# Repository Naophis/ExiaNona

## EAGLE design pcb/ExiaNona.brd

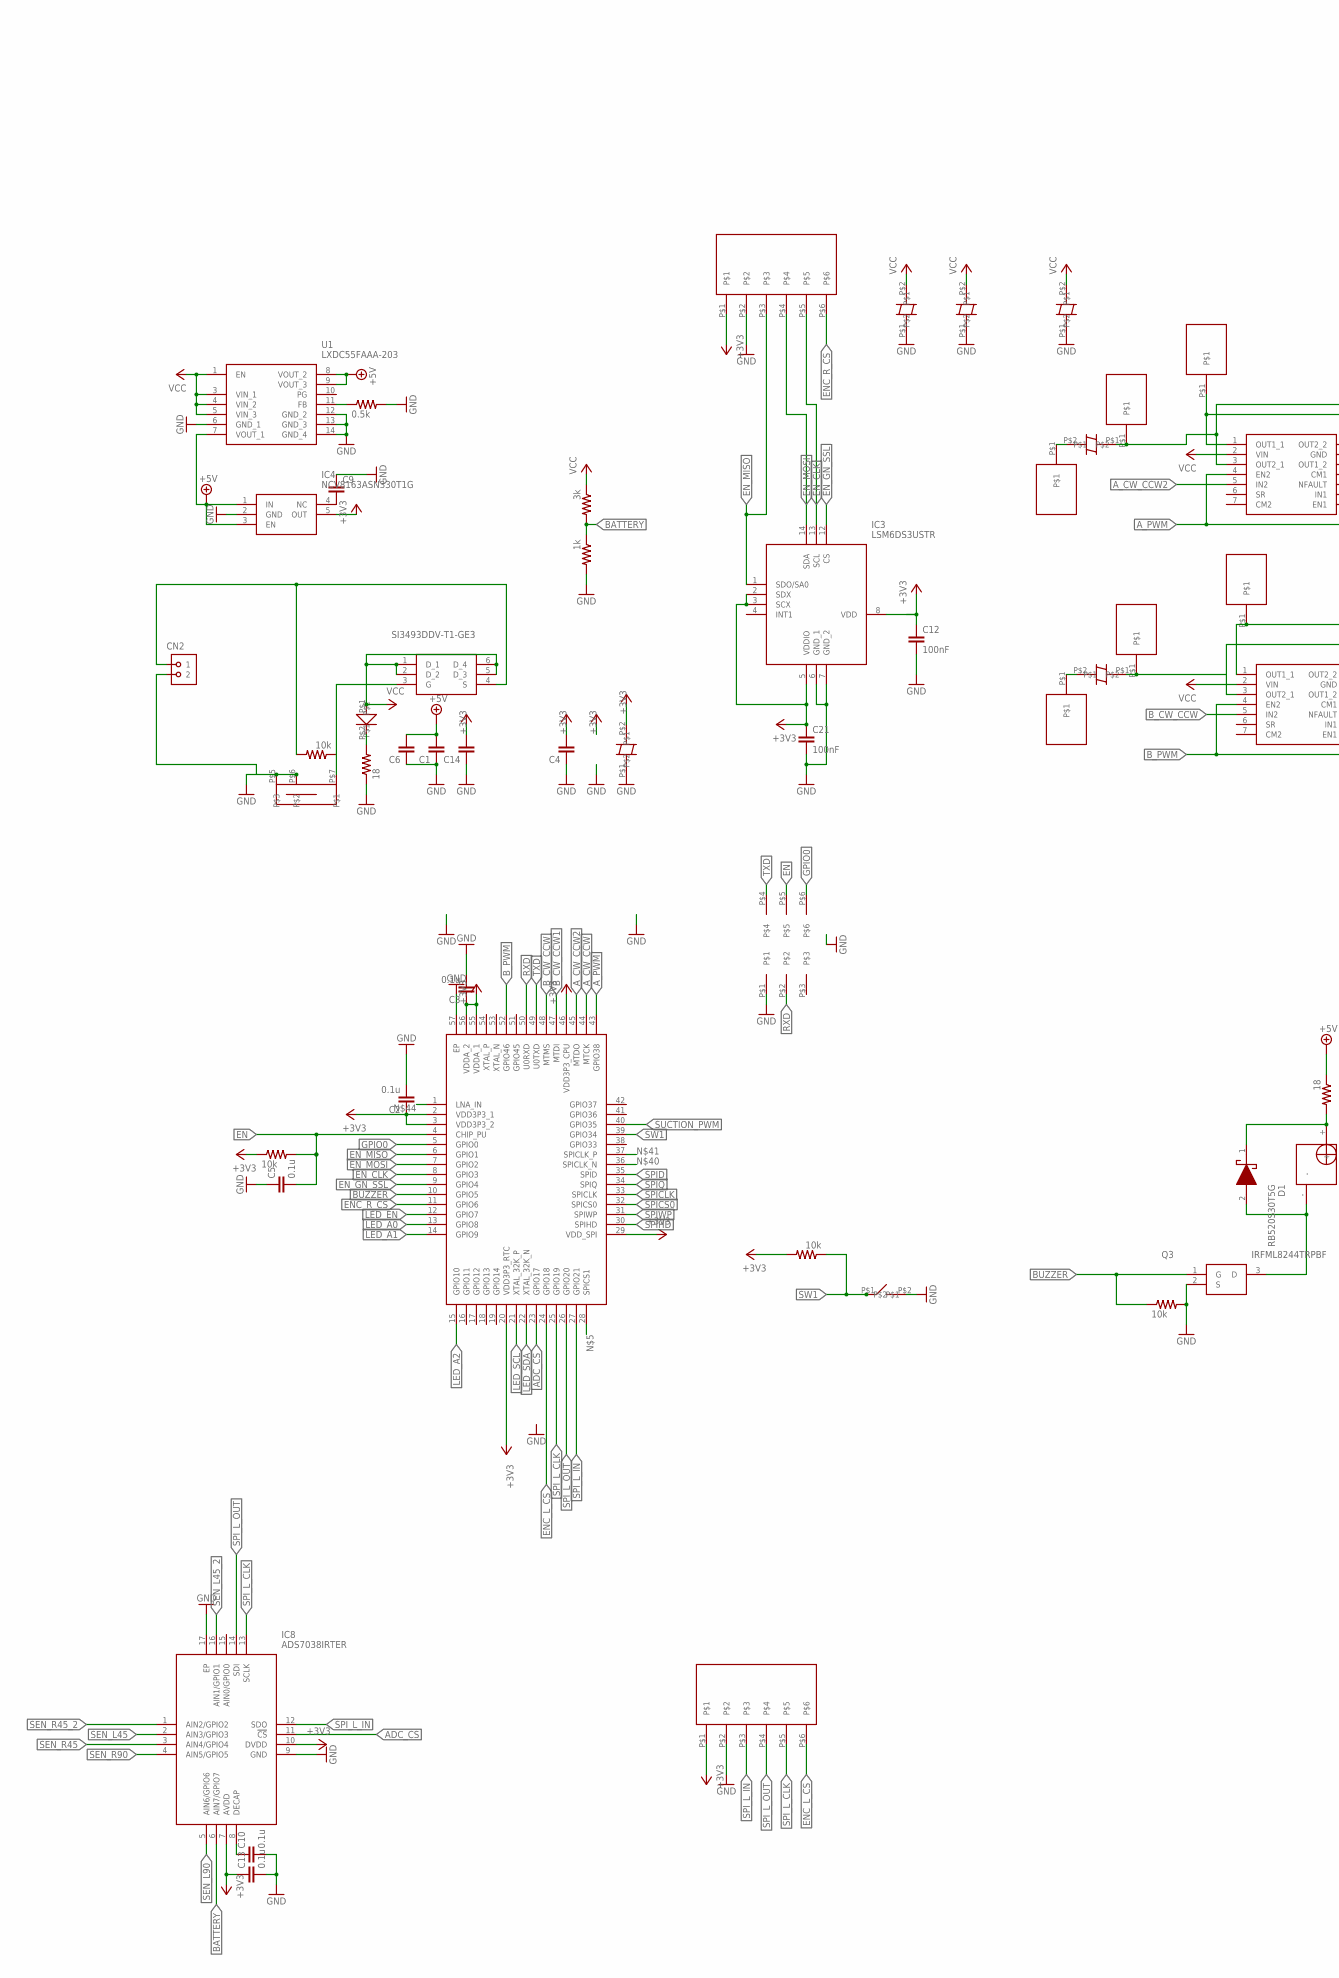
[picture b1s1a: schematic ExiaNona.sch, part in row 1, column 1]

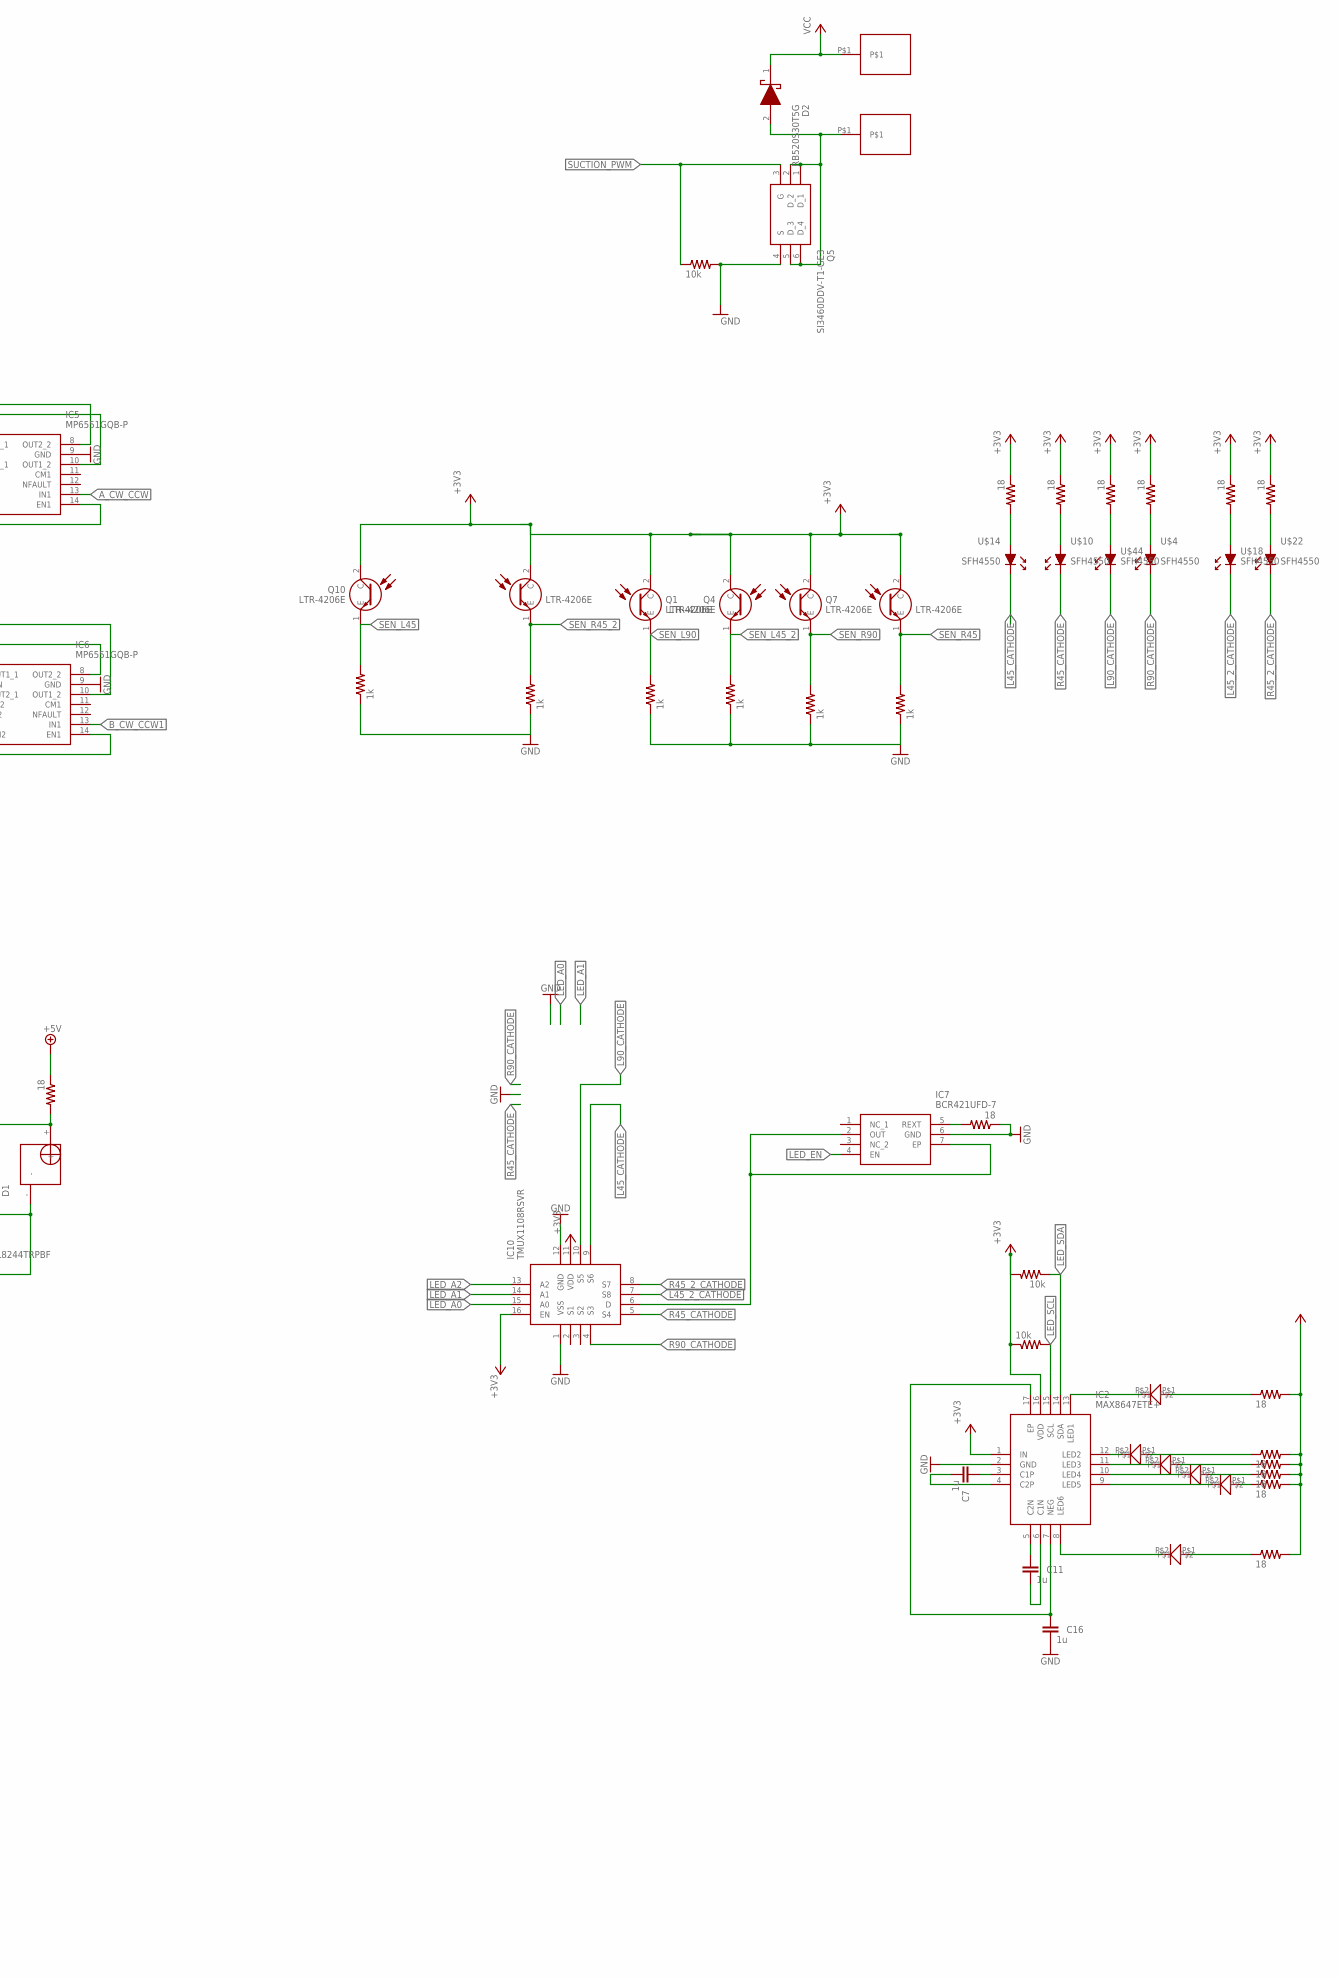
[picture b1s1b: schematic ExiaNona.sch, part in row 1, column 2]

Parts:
C1, C4, C6, C14: C3216
C2, C3, C5, C10, C13: 0.1u; R1005
C7, C11, C16: 1u; R1005
C9: C1608
C12, C21: 100nF; R1005
CN2: HRCON-2
D1, D2: RB520S30T5G; SODFL1608X70N
IC1: ESP32-S3-WROOM-1-N8; QFN40P700X700X90-57N
IC2: MAX8647ETE+; QFN50P300X300X80-17N
IC3: LSM6DS3USTR; LGA-14(2.5X3X0.86)
IC4: NCV8163ASN330T1G; SOT95P275X110-5N
IC5, IC6: MP6551GQB-P; MP6551GQBP
IC7: BCR421UFD-7; BCR421UFD7
IC8: ADS7038IRTER; QFN50P300X300X80-17N
IC10: TMUX1108RSVR; QFN40P180X260X55-16N
Q1, Q4, Q7, Q8, Q10, Q11: LTR-4206E; LTR4206E
Q2: SI3493DDV-T1-GE3; SOT95P284X110-6N
Q3: IRFML8244TRPBF; SOT95P237X112-3N
Q5: SI3460DDV-T1-GE3; SOT95P284X110-6N
R1, R7, R8, R9, R12, R13, R21: 10k; R1005
R2: 3k; R1005
R3, R4, R16, R17, R18, R20, R22: 1k; R1005
R5: 0.5k; R1005
R6, R10, R11, R14, R15, R19, R25, R26, R27, R28, R29, R30, R31, R32, R33: 18; R1608
U1: LXDC55FAAA-203; LXDC55FAAA203
U$1, U$8, U$9, U$11, U$17, U$20, U$27, U$58: PAD
U$2, U$19, U$21, U$23, U$25, U$30, U$31: LED_1005
U$3, U$5, U$7, U$12, U$16, U$24: PANA
U$4, U$10, U$14, U$18, U$22, U$44: SFH4550; SFH_4550
U$6: PIN2_3
U$13: BUZZER_44; BUZZER
U$15, U$28: ENCORDER_1; ENCORDER_R
U$43: TVAF06
U$53: SWICH; SWITCH

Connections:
+3V3: C2.P$1 (1), C3.P$1 (1), C4.2, C12.P$1 (1), C13.P$1 (1), C14.2, C21.P$1 (1), IC1.2 (VDD3P3_1), IC1.3 (VDD3P3_2), IC1.20 (VDD3P3_RTC), IC1.29 (VDD_SPI), IC1.46 (VDD3P3_CPU), IC1.55 (VDDA_1), IC1.56 (VDDA_2), IC2.1 (IN), IC2.16 (VDD), IC3.2 (SDX), IC3.3 (SCX), IC3.5 (VDDIO), IC3.8 (VDD), IC4.5 (OUT), IC8.7 (AVDD), IC8.10 (DVDD), IC10.11 (VDD), IC10.16 (EN), Q1.2 (C), Q4.2 (C), Q7.2 (C), Q8.2 (C), Q10.2 (C), Q11.2 (C), R1.P$1 (1), R8.P$2 (2), R11.1, R12.P$1 (1), R13.P$2 (2), R14.1, R15.1, R25.1, R26.1, R27.2, R28.2, R29.1, R30.2, R31.2, R32.2, R33.2, U$15.P$1, U$24.P$2, U$28.P$1
+5V: C1.2, C6.2, IC4.1 (IN), IC4.3 (EN), R10.1, U1.7 (VOUT_1), U1.8 (VOUT_2), U1.9 (VOUT_3)
ADC_CS: IC1.23 (GPIO17), IC8.11 (!CS)
A_CW_CCW: IC1.44 (MTCK), IC5.13 (IN1)
A_CW_CCW2: IC1.45 (MTDO), IC5.5 (IN2)
A_PWM: IC1.43 (GPIO38), IC5.4 (EN2), IC5.14 (EN1)
BATTERY: IC8.6 (AIN7/GPIO7), R2.P$2 (2), R3.P$1 (1)
BUZZER: IC1.10 (GPIO5), Q3.1 (G), R9.P$1 (1)
B_CW_CCW: IC1.48 (MTMS), IC6.5 (IN2)
B_CW_CCW1: IC1.47 (MTDI), IC6.13 (IN1)
B_PWM: IC1.52 (GPIO46), IC6.4 (EN2), IC6.14 (EN1)
EN: C5.P$2 (2), IC1.4 (CHIP_PU), R1.P$2 (2), U$6.P$5
ENC_L_CS: IC1.24 (GPIO18), U$15.P$6
ENC_R_CS: IC1.11 (GPIO6), U$28.P$6
EN_CLK: IC1.8 (GPIO3), IC3.13 (SCL), U$28.P$5
EN_GN_SSL: IC1.9 (GPIO4), IC3.12 (CS)
EN_MISO: IC1.6 (GPIO1), IC3.1 (SDO/SA0), U$28.P$3
EN_MOSI: IC1.7 (GPIO2), IC3.14 (SDA), U$28.P$4
GND: C1.1, C2.P$2 (2), C3.P$2 (2), C4.1, C5.P$1 (1), C6.1, C9.1, C10.P$2 (2), C12.P$2 (2), C13.P$2 (2), C14.1, C16.P$2 (2), C21.P$2 (2), CN2.2, IC1.57 (EP), IC2.2 (GND), IC3.6 (GND_1), IC3.7 (GND_2), IC4.2 (GND), IC5.9 (GND), IC6.9 (GND), IC7.6 (GND), IC8.9 (GND), IC8.17 (EP), IC10.1 (VSS), IC10.12 (GND), Q3.2 (S), Q5.4 (S), R3.P$2 (2), R4.P$1 (1), R5.P$2 (2), R6.1, R9.P$2 (2), R16.P$1 (1), R17.P$1 (1), R18.P$1 (1), R19.1, R20.P$1 (1), R21.P$2 (2), R22.P$1 (1), U1.6 (GND_1), U1.12 (GND_2), U1.13 (GND_3), U1.14 (GND_4), U$5.P$1, U$6.P$1, U$12.P$1, U$15.P$2, U$16.P$1, U$24.P$1, U$28.P$2, U$43.P$2, U$53.P$5, U$53.P$6
GPIO0: IC1.5 (GPIO0), U$6.P$6
L45_2_CATHODE: IC10.7 (S8), U$18.CASODE (K)
L45_CATHODE: IC10.9 (S6), U$14.CASODE (K)
L90_CATHODE: IC10.10 (S5), U$44.CASODE (K)
LED_A0: IC1.13 (GPIO8), IC10.15 (A0)
LED_A1: IC1.14 (GPIO9), IC10.14 (A1)
LED_A2: IC1.15 (GPIO10), IC10.13 (A2)
LED_EN: IC1.12 (GPIO7), IC7.4 (EN)
LED_SCL: IC1.21 (XTAL_32K_P), IC2.15 (SCL), R12.P$2 (2)
LED_SDA: IC1.22 (XTAL_32K_N), IC2.14 (SDA), R13.P$1 (1)
unnamed: D1.1 (K), R10.2, U$13.+
unnamed: IC6.3 (OUT2_1), IC6.8 (OUT2_2), U$7.P$1, U$8.P$1
unnamed: D1.2 (A), Q3.3 (D), U$13.-
unnamed: R6.2, U$2.P$2
unnamed: R11.2, U$18.ANODE (A)
unnamed: R33.1, U$30.P$1
unnamed: R32.1, U$23.P$1
unnamed: R31.1, U$21.P$1
unnamed: R30.1, U$19.P$1
unnamed: R28.1, U$25.P$1
unnamed: R14.2, U$22.ANODE (A)
unnamed: U$1.P$1, U$7.P$2
unnamed: R27.1, U$31.P$1
unnamed: Q2.3 (G), R7.P$1 (1), U$53.P$7
unnamed: C9.2, IC4.4 (NC)
unnamed: CN2.1, Q2.4 (S), R7.P$2 (2)
unnamed: R29.2, U$14.ANODE (A)
unnamed: R15.2, U$10.ANODE (A)
unnamed: R25.2, U$44.ANODE (A)
unnamed: R26.2, U$4.ANODE (A)
unnamed: U$3.P$2, U$11.P$1
unnamed: IC5.3 (OUT2_1), IC5.8 (OUT2_2), U$3.P$1, U$9.P$1
unnamed: IC7.5 (REXT), R19.2
unnamed: R5.P$1 (1), U1.11 (FB)
unnamed: IC5.1 (OUT1_1), IC5.10 (OUT1_2), U$27.P$1
unnamed: IC6.1 (OUT1_1), IC6.10 (OUT1_2), U$17.P$1
unnamed: D2.2 (A), Q5.1 (D_1), Q5.2 (D_2), Q5.5 (D_3), Q5.6 (D_4), U$58.P$1
unnamed: IC7.2 (OUT), IC7.7 (EP), IC10.6 (D)
unnamed: C10.P$1 (1), IC8.8 (DECAP)
unnamed: C7.P$1 (1), IC2.3 (C1P)
unnamed: C7.P$2 (2), IC2.4 (C2P)
unnamed: C11.P$1 (1), IC2.5 (C2N)
unnamed: C11.P$2 (2), IC2.6 (C1N)
unnamed: C16.P$1 (1), IC2.7 (NEG), IC2.17 (EP)
unnamed: IC2.8 (LED6), U$31.P$2
unnamed: IC2.13 (LED1), U$30.P$2
unnamed: IC2.12 (LED2), U$23.P$2
unnamed: IC2.11 (LED3), U$21.P$2
unnamed: IC2.10 (LED4), U$19.P$2
unnamed: IC2.9 (LED5), U$25.P$2
R45_2_CATHODE: IC10.8 (S7), U$22.CASODE (K)
R45_CATHODE: IC10.5 (S4), U$10.CASODE (K)
R90_CATHODE: IC10.4 (S3), U$4.CASODE (K)
RXD: IC1.50 (U0RXD), U$6.P$2
SEN_L45: IC8.2 (AIN3/GPIO3), Q10.1 (E), R4.P$2 (2)
SEN_L45_2: IC8.16 (AIN1/GPIO1), Q4.1 (E), R17.P$2 (2)
SEN_L90: IC8.5 (AIN6/GPIO6), Q1.1 (E), R18.P$2 (2)
SEN_R45: IC8.3 (AIN4/GPIO4), Q8.1 (E), R16.P$2 (2)
SEN_R45_2: IC8.1 (AIN2/GPIO2), Q11.1 (E), R20.P$2 (2)
SEN_R90: IC8.4 (AIN5/GPIO5), Q7.1 (E), R22.P$2 (2)
SPICLK: IC1.33 (SPICLK)
SPICS0: IC1.32 (SPICS0)
SPID: IC1.35 (SPID)
SPIHD: IC1.30 (SPIHD)
SPIQ: IC1.34 (SPIQ)
SPIWP: IC1.31 (SPIWP)
SPI_L_CLK: IC1.25 (GPIO19), IC8.13 (SCLK), U$15.P$5
SPI_L_IN: IC1.27 (GPIO21), IC8.12 (SDO), U$15.P$3
SPI_L_OUT: IC1.26 (GPIO20), IC8.14 (SDI), U$15.P$4
SUCTION_PWM: IC1.40 (GPIO35), Q5.3 (G), R21.P$1 (1)
SW1: IC1.39 (GPIO34), R8.P$1 (1), U$43.P$1
TXD: IC1.49 (U0TXD), U$6.P$4
VCC: D2.1 (K), IC5.2 (VIN), IC6.2 (VIN), Q2.1 (D_1), Q2.2 (D_2), Q2.5 (D_3), Q2.6 (D_4), R2.P$1 (1), U1.1 (EN), U1.3 (VIN_1), U1.4 (VIN_2), U1.5 (VIN_3), U$2.P$1, U$5.P$2, U$12.P$2, U$16.P$2, U$20.P$1

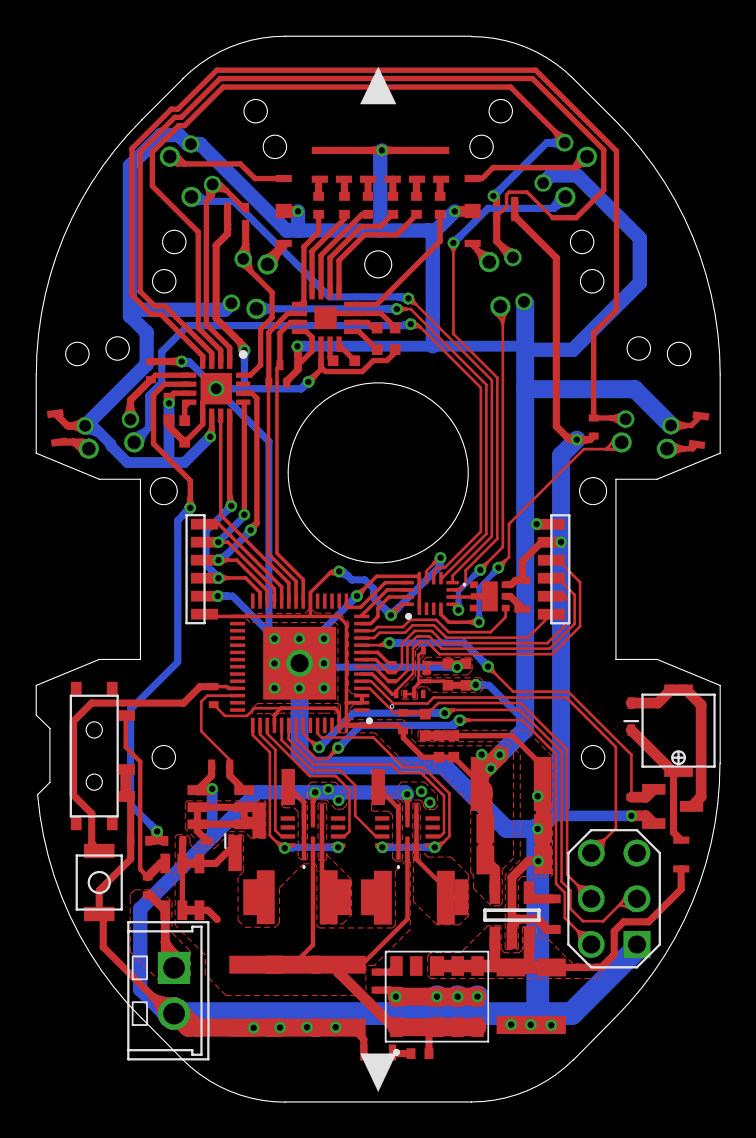
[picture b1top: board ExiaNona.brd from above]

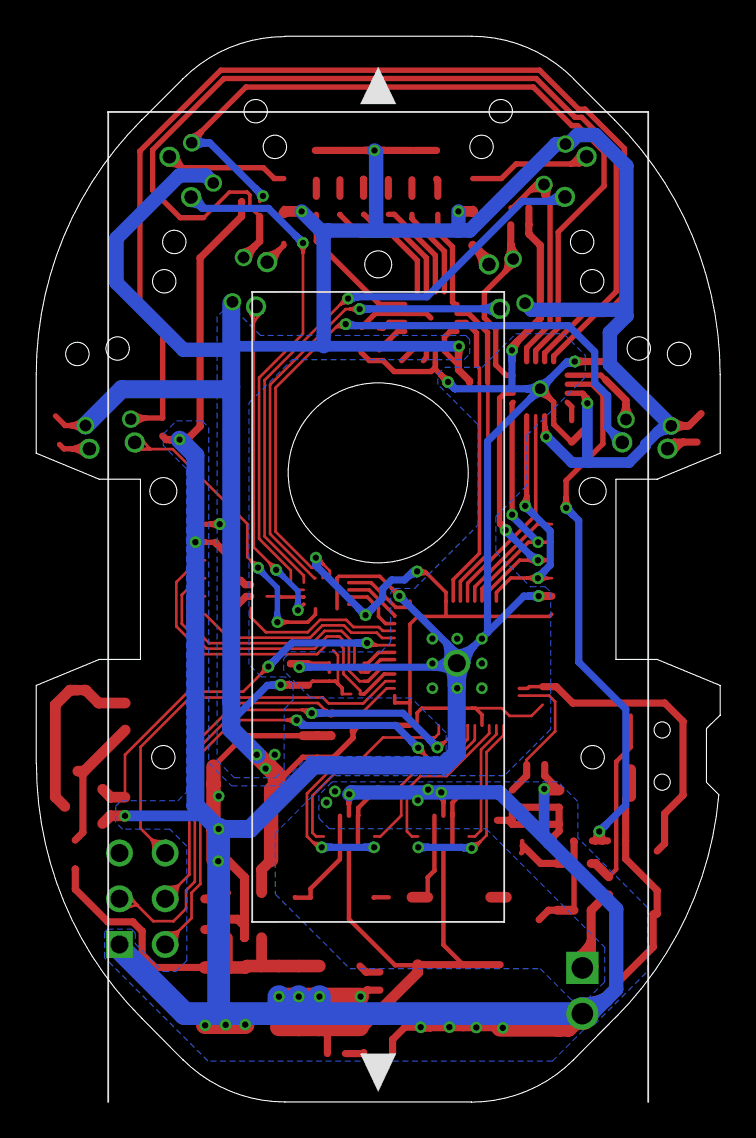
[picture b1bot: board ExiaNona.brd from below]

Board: 2 copper layers, 38.0 x 59.2 mm, 101 parts (2 on the bottom side), 86 nets.

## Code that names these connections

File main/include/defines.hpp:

#ifndef DEFINES_HPP
#define DEFINES_HPP

#include "driver/gpio.h"
#include "driver/ledc.h"
#include "gen_code_mpc/bus.h"
#include "include/maze_solver.hpp"
#include "sdkconfig.h"
#include "soc/adc_channel.h"
#include "soc/gpio_struct.h"
#include "soc/ledc_periph.h"

#include "fs.hpp"
#include "include/enums.hpp"
#include "include/structs.hpp"
#include "sdkconfig.h"
#include <bitset>
#include <initializer_list>
#include <iostream>
#include <memory>
#include <sstream>
#include <string>
#include <string_view>
#include <unordered_map>
#include <vector>

#include "esp_heap_caps.h"
#include "icm20689.hpp"
#include "lsm6dsr.hpp"

#define portTICK_RATE_MS portTICK_PERIOD_MS
#define xTaskHandle TaskHandle_t

#define ABS(IN) ((IN) < 0 ? -(IN) : (IN))

constexpr int GY_DQ_SIZE = 2;
constexpr int GY_CYCLE = 2500; // 2500=1/4msec
// constexpr int GY_CYCLE = 1250; // 1250=1/8msec
constexpr int GY_MODE = 0;
constexpr float cell_size = 90;

constexpr gpio_num_t SDA_PIN = GPIO_NUM_16;
constexpr gpio_num_t SCL_PIN = GPIO_NUM_15;

constexpr gpio_num_t LED_EN = GPIO_NUM_7;
constexpr gpio_num_t LED_A0 = GPIO_NUM_8;
constexpr gpio_num_t LED_A1 = GPIO_NUM_9;
constexpr gpio_num_t LED_A2 = GPIO_NUM_10;

constexpr gpio_num_t TXD = GPIO_NUM_43;
constexpr gpio_num_t RXD = GPIO_NUM_44;
constexpr gpio_num_t RTS = GPIO_NUM_15;
constexpr gpio_num_t CTS = GPIO_NUM_16;

constexpr gpio_num_t L_CW_CCW1 = GPIO_NUM_39;
constexpr gpio_num_t L_CW_CCW2 = GPIO_NUM_40;
constexpr gpio_num_t R_CW_CCW1 = GPIO_NUM_41;
constexpr gpio_num_t R_CW_CCW2 = GPIO_NUM_42;

constexpr uint32_t L_CW_CCW1_BIT = BIT(L_CW_CCW1 - 32);
constexpr uint32_t L_CW_CCW2_BIT = BIT(L_CW_CCW2 - 32);
constexpr uint32_t R_CW_CCW1_BIT = BIT(R_CW_CCW1 - 32);
constexpr uint32_t R_CW_CCW2_BIT = BIT(R_CW_CCW2 - 32);

constexpr gpio_num_t Motor_L_PWM = GPIO_NUM_38;
constexpr gpio_num_t Motor_L_PWM2 = GPIO_NUM_38;
constexpr gpio_num_t Motor_R_PWM = GPIO_NUM_46;
constexpr gpio_num_t Motor_R_PWM2 = GPIO_NUM_46;

constexpr gpio_num_t BUZZER = GPIO_NUM_5;

constexpr gpio_num_t SW1 = GPIO_NUM_34;

constexpr gpio_num_t SPI_R_MISO = GPIO_NUM_1;
constexpr gpio_num_t SPI_R_MOSI = GPIO_NUM_2;
constexpr gpio_num_t SPI_R_CLK = GPIO_NUM_3;
constexpr gpio_num_t SPI_R_GYRO_SSL = GPIO_NUM_4;
constexpr gpio_num_t SPI_R_ENC_SSL = GPIO_NUM_6;

constexpr gpio_num_t SPI_L_MISO = GPIO_NUM_21; 
constexpr gpio_num_t SPI_L_MOSI = GPIO_NUM_20; 
constexpr gpio_num_t SPI_L_CLK = GPIO_NUM_19;
constexpr gpio_num_t SPI_L_ENC_SSL = GPIO_NUM_18;
constexpr gpio_num_t SPI_L_ADC_SSL = GPIO_NUM_17;

constexpr gpio_num_t SUCTION_PWM = GPIO_NUM_35;

#define SEN_R90 ADC2_CHANNEL_2
#define SEN_L90 ADC2_CHANNEL_4
#define SEN_R45 ADC2_CHANNEL_6
#define SEN_L45 ADC2_CHANNEL_7
#define BATTERY ADC2_CHANNEL_9

#define MAX(a, b) ((a) > (b) ? (a) : (b))
#define MIN(a, b) ((a) < (b) ? (a) : (b))

// constexpr adc2_channel_t SEN_R90 = ADC2_CHANNEL_0;
// constexpr adc2_channel_t SEN_R45 = ADC2_CHANNEL_1;
// constexpr adc2_channel_t SEN_F = ADC2_CHANNEL_4;
// constexpr adc2_channel_t SEN_L45 = ADC2_CHANNEL_6;
// constexpr adc2_channel_t SEN_L90 = ADC2_CHANNEL_8;
// constexpr adc2_channel_t BATTERY = ADC2_CHANNEL_9;

constexpr int16_t ENCODER_H_LIM_VAL = 32767;
constexpr int16_t ENCODER_L_LIM_VAL = -32767;

const int16_t ENC_RESOLUTION = 16384 - 1;
constexpr uint8_t READ_FLAG = 0x80;
constexpr uint16_t READ_FLAG2 = 0b01000000;
constexpr uint16_t PARITY_FLAG = 0b10000000;
constexpr uint8_t ESC = 0x1B;
constexpr uint16_t BUF_SIZE = 4096;

constexpr uint16_t MOTION_CHECK_TH = 1000;
constexpr uint16_t ENC_OPE_V_R_TH = 175;

constexpr uint16_t LOG_SIZE = 1300;
constexpr uint16_t LINE_BUF_SIZE = 1024;
// constexpr float BATTERY_GAIN = 3.2075; // 2.97324;
constexpr float BATTERY_GAIN = 3.317057486323464; // 2.97324;

constexpr uint8_t LEDC_HIGH_SPEED_MODE = 0;
constexpr float LOW_BATTERY_TH = 11.7;

constexpr uint16_t RESET_GYRO_LOOP_CNT = 512;

static const std::initializer_list<std::pair<TurnType, std::string>>
    turn_name_list = {
        {TurnType::None, "straight"},    //
        {TurnType::Normal, "normal"},    //
        {TurnType::Large, "large"},      //
        {TurnType::Orval, "orval"},      //
        {TurnType::Dia45, "dia45"},      //
        {TurnType::Dia135, "dia135"},    //
        {TurnType::Dia90, "dia90"},      //
        {TurnType::Dia45_2, "dia45_2"},  //
        {TurnType::Dia135_2, "dia135_2"} //
};

static const std::initializer_list<std::pair<StraightType, std::string>>
    straight_name_list = {
        {StraightType::Search, "search"},          //
        {StraightType::FastRun, "fast_run"},       //
        {StraightType::FastRunDia, "fast_run_dia"} //
};

static const std::string slalom_log_file("/spiflash/sla.log");
static const std::string sysid_log_file("/spiflash/sysid.log");
static const std::string maze_log_file("/spiflash/maze.txt");
static const std::string maze_log_kata_file("/spiflash/maze_kata.log");
static const std::string maze_log_return_file("/spiflash/maze_return.log");

static const std::string format1("%d,%0.3f,%0.3f,%0.3f,%0.3f,%0.3f,%d,%d,%0.3f,"
                                 "%0.3f,%0.3f,%0.3f,");
static const std::string
    format2("%0.3f,%0.3f,%0.3f,%0.3f,%0.3f,%0.3f,%0.3f,%0.3f,%0.3f,");
static const std::string format3("%0.3f,%0.3f,%0.3f,%0.3f,%0.3f,%0.3f,%0.3f,%0."
                                 "3f,%0.3f,%0.3f,%0.3f,%0.3f,%0.3f,%0.3f,%0.3f,"
                                 "%0.3f,%d,");
static const std::string format4("%0.3f,%0.3f,%0.3f,%0.3f,%d,%d,%d,%d,%d,%d,");
static const std::string format5(
    "%0.3f,%0.3f,%0.3f,%0.3f,%0.3f,%0.3f,%0.3f,%0.3f,%0.3f,%0.3f,%0.3f,%0.3f,");
static const std::string format6(
    "%0.3f,%0.3f,%0.3f,%0.3f,%0.3f,%0.3f,%0.3f,%0.3f,%0.3f,%0.3f,%0.3f,%0.3f,");
static const std::string format7("%0.3f,%0.3f,%0.3f,%0.3f\n");
static const std::string
    formatsysid("%d,%0.3f,%0.3f,%0.3f,%0.3f,%0.3f,%0.3f\n");
static char line_buf[LINE_BUF_SIZE];
// static const std::string format1("%d,%d,%d,%d,%d,%d,");
// static const std::string format2("%d,%d,%d,%d,%d,%d,%d,");
// static const std::string format3("%d,%d,%d,%d,%d,%d,%d,%d,%d,%d,%d,%d\n");

std::shared_ptr<sensing_result_entity_t> get_sensing_entity();

#endif

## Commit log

2024-04-21 change pcb board
2024-05-12 update for Nona
2024-05-25 update tools
2024-06-20 feat: change rtos queue to notify
2024-06-20 feat: change default flash USB device
2024-06-21 chore: ommit comment out
2024-06-24 feat: use IRAM_ATTR
2024-06-25 fix: dont use DMA
2024-07-26 fixed serial port package
2024-07-27 update for 6 sensor
